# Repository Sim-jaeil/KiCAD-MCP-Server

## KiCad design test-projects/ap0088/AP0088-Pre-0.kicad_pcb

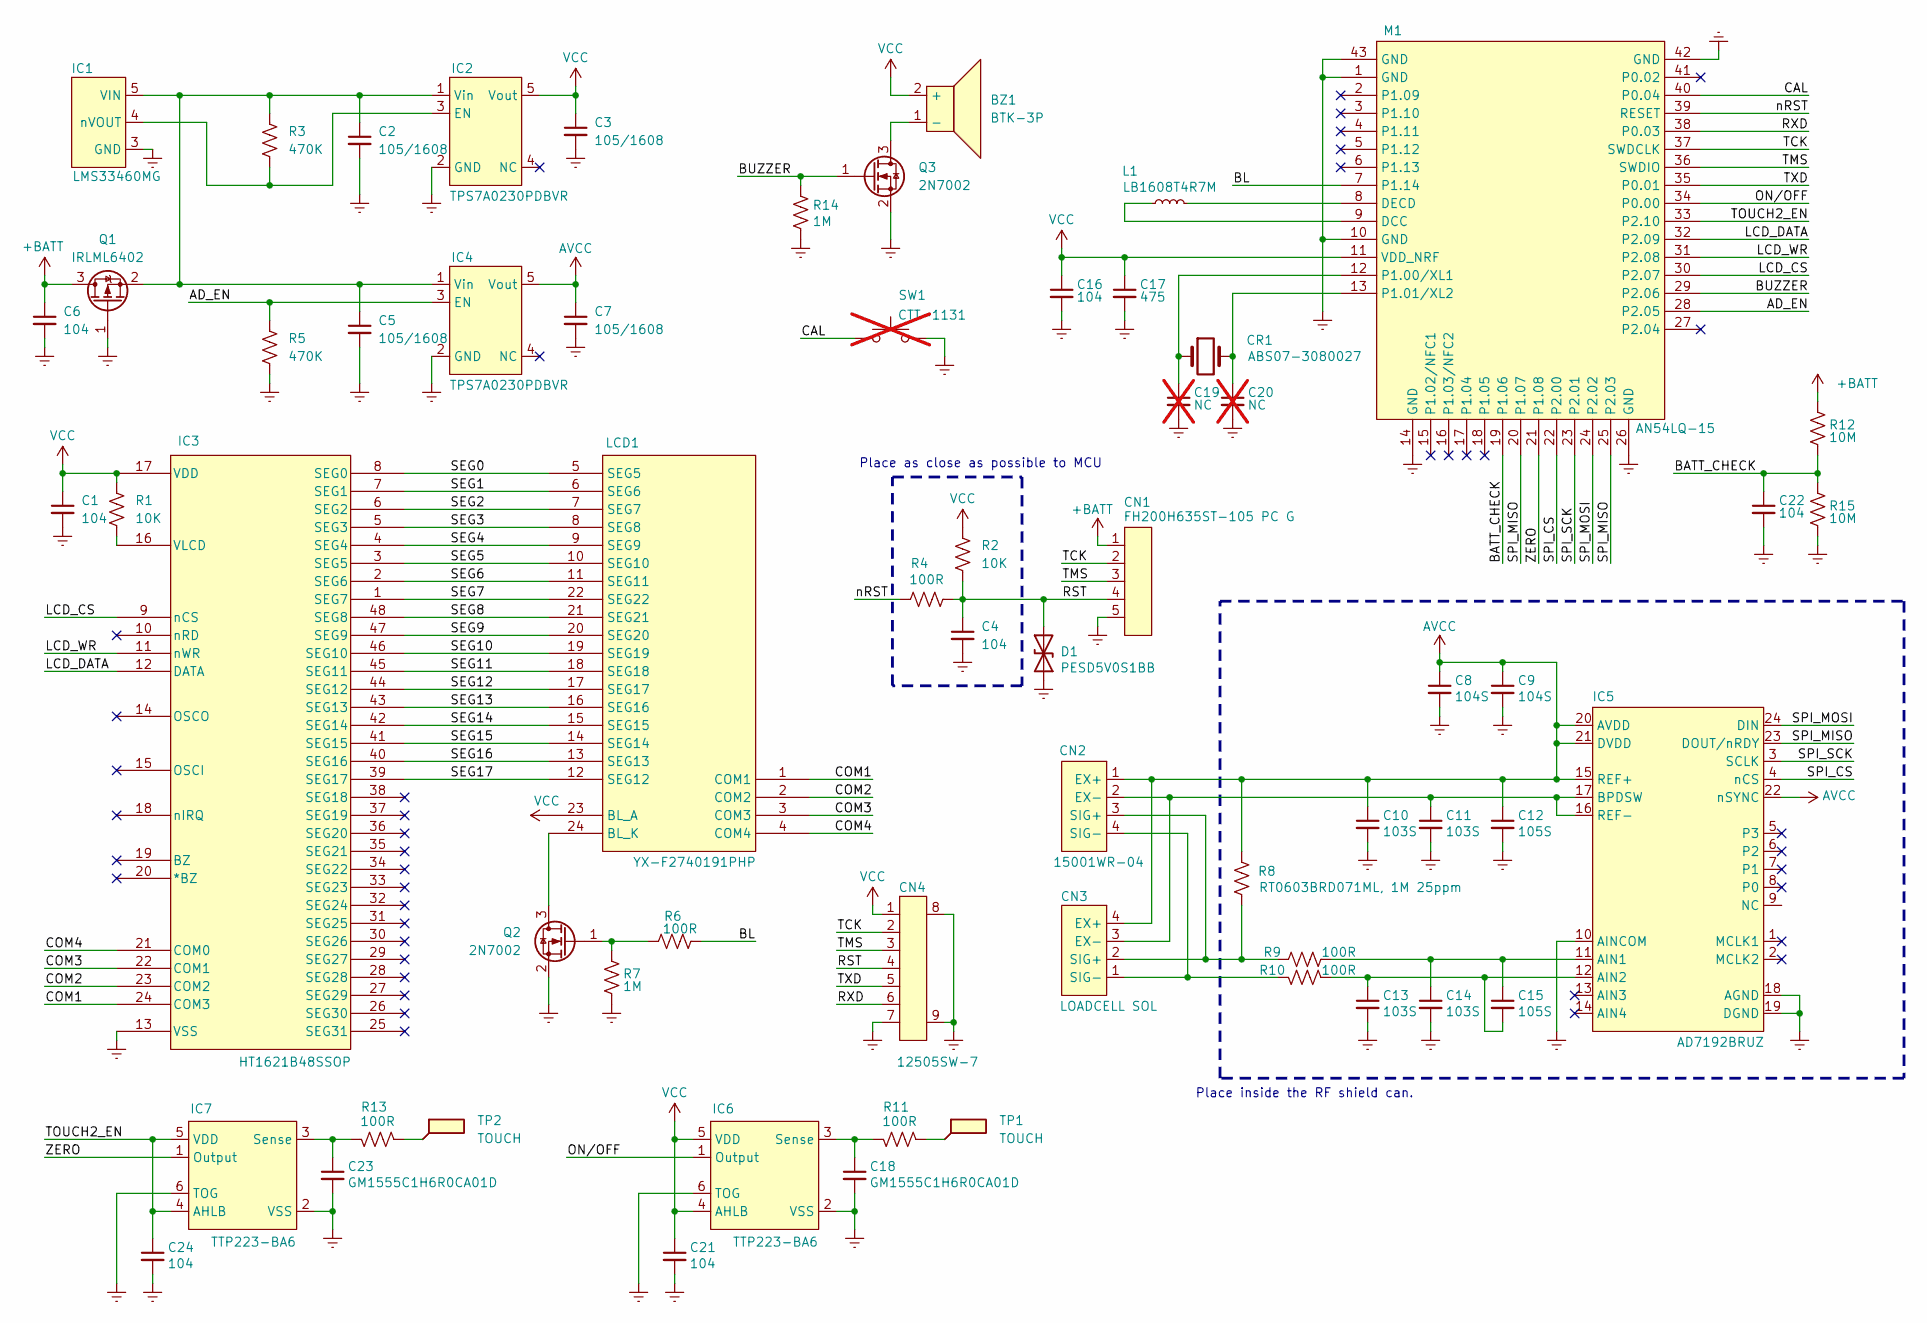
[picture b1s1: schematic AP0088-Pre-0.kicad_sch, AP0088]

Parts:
BZ1: BTK-3P
C1, C4, C6, C16, C21, C22, C24: 104; 1005C
C2, C3, C5, C7: 105/1608; 1608C
C8, C9: 104S; 1005C
C10, C11, C13, C14: 103S; 1005C
C12, C15: 105S; 1005C
C17: 475; 1608C
C18, C23: GM1555C1H6R0CA01D; 1005C
C19, C20: NC; 1005C; not fitted
CN1: FH200H635ST-105 PC G
CN2: 15001WR-04
CN3: LOADCELL SOL
CN4: 12505SW-7
CR1: ABS07-3080027; Crystal_SMD_3215-2Pin_3.2x1.5mm
D1: PESD5V0S1BB; D_SOD-523
IC1: LMS33460MG; SOT-353_SC-70-5
IC2, IC4: TPS7A0230PDBVR; SOT-23-5
IC3: HT1621B48SSOP; HT1621B
IC5: AD7192BRUZ; TSSOP-24_4.4x7.8mm_P0.65mm
IC6, IC7: TTP223-BA6
L1: LB1608T4R7M; L_0603_1608Metric
LCD1: YX-F2740191PHP; AXR-LCD
M1: AN54LQ-15
Q1: IRLML6402; SOT-23
Q2, Q3: 2N7002; SOT-23
R1, R2: 10K; 1005R
R3, R5: 470K; 1005R
R4, R6, R9, R10, R11, R13: 100R; 1005R
R7, R14: 1M; 1005R
R8: RT0603BRD071ML, 1M 25ppm; 1608R
R12, R15: 10M; 1005R
SW1: CTT-1131; not fitted
TP1, TP2: TOUCH; TOUCH_SPRING

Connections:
+BATT: C6.1, CN1.1, Q1.3 (D), R12.1
/AD_EN: IC4.3 (EN), M1.28 (P2.05), R5.2
/BATT_CHECK: C22.1, M1.19 (P1.06), R12.2, R15.1
/BL: M1.7 (P1.14), R6.2
/BUZZER: M1.29 (P2.06), Q3.1 (G), R14.1
/CAL: M1.40 (P0.04), SW1.1
/COM1: IC3.24 (COM3), LCD1.1 (COM1)
/COM2: IC3.23 (COM2), LCD1.2 (COM2)
/COM3: IC3.22 (COM1), LCD1.3 (COM3)
/COM4: IC3.21 (COM0), LCD1.4 (COM4)
/LCD_CS: IC3.9 (nCS), M1.30 (P2.07)
/LCD_DATA: IC3.12 (DATA), M1.32 (P2.09)
/LCD_WR: IC3.11 (nWR), M1.31 (P2.08)
/ON/OFF: IC6.1 (Output), M1.34 (P0.00)
/RST: C4.1, CN1.4, CN4.4, D1.2 (A2), R2.1, R4.2
/RXD: CN4.6, M1.38 (P0.03)
/SEG0: IC3.8 (SEG0), LCD1.5 (SEG5)
/SEG1: IC3.7 (SEG1), LCD1.6 (SEG6)
/SEG2: IC3.6 (SEG2), LCD1.7 (SEG7)
/SEG3: IC3.5 (SEG3), LCD1.8 (SEG8)
/SEG4: IC3.4 (SEG4), LCD1.9 (SEG9)
/SEG5: IC3.3 (SEG5), LCD1.10 (SEG10)
/SEG6: IC3.2 (SEG6), LCD1.11 (SEG11)
/SEG7: IC3.1 (SEG7), LCD1.22 (SEG22)
/SEG8: IC3.48 (SEG8), LCD1.21 (SEG21)
/SEG9: IC3.47 (SEG9), LCD1.20 (SEG20)
/SEG10: IC3.46 (SEG10), LCD1.19 (SEG19)
/SEG11: IC3.45 (SEG11), LCD1.18 (SEG18)
/SEG12: IC3.44 (SEG12), LCD1.17 (SEG17)
/SEG13: IC3.43 (SEG13), LCD1.16 (SEG16)
/SEG14: IC3.42 (SEG14), LCD1.15 (SEG15)
/SEG15: IC3.41 (SEG15), LCD1.14 (SEG14)
/SEG16: IC3.40 (SEG16), LCD1.13 (SEG13)
/SEG17: IC3.39 (SEG17), LCD1.12 (SEG12)
/SPI_CS: IC5.4 (nCS), M1.22 (P2.00)
/SPI_MISO: IC5.23 (DOUT/nRDY), M1.20 (P1.07), M1.25 (P2.03)
/SPI_MOSI: IC5.24 (DIN), M1.24 (P2.02)
/SPI_SCK: IC5.3 (SCLK), M1.23 (P2.01)
/TCK: CN1.2, CN4.2, M1.37 (SWDCLK)
/TMS: CN1.3, CN4.3, M1.36 (SWDIO)
/TOUCH2_EN: C24.1, IC7.4 (AHLB), IC7.5 (VDD), M1.33 (P2.10)
/TXD: CN4.5, M1.35 (P0.01)
/ZERO: IC7.1 (Output), M1.21 (P1.08)
/nRST: M1.39 (RESET), R4.1
AVCC: C7.1, C8.1, C9.1, C10.1, C12.1, CN2.1 (EX+), CN3.4 (EX+), IC4.5 (Vout), IC5.15 (REF+), IC5.20 (AVDD), IC5.21 (DVDD), IC5.22 (nSYNC), R8.2
Earth: C1.2, C2.2, C3.2, C4.2, C5.2, C6.2, C7.2, C8.2, C9.2, C10.2, C11.2, C12.2, C13.2, C14.2, C16.2, C17.2, C18.2, C19.2, C20.2, C21.2, C22.2, C23.2, C24.2, CN1.5, CN4.7, CN4.8, CN4.9, D1.1 (A1), IC1.3 (GND), IC2.2 (GND), IC3.13 (VSS), IC4.2 (GND), IC5.10 (AINCOM), IC5.18 (AGND), IC5.19 (DGND), IC6.2 (VSS), IC6.6 (TOG), IC7.2 (VSS), IC7.6 (TOG), M1.1 (GND), M1.10 (GND), M1.14 (GND), M1.26 (GND), M1.42 (GND), M1.43 (GND), Q1.1 (G), Q2.2 (S), Q3.2 (S), R5.1, R7.2, R14.2, R15.2, SW1.2
unnamed: BZ1.1 (-), Q3.3 (D)
unnamed: C11.1, CN2.2 (EX-), CN3.3 (EX-), IC5.16 (REF-), IC5.17 (BPDSW)
unnamed: CN2.3 (SIG+), CN3.2 (SIG+), R8.1, R9.2
unnamed: CN2.4 (SIG-), CN3.1 (SIG-), R10.2
unnamed: C2.1, C5.1, IC1.5 (VIN), IC2.1 (Vin), IC4.1 (Vin), Q1.2 (S), R3.2
unnamed: IC1.4 (nVOUT), IC2.3 (EN), R3.1
unnamed: IC3.16 (VLCD), R1.1
unnamed: C14.1, C15.1, IC5.11 (AIN1), R9.1
unnamed: C13.1, C15.2, IC5.12 (AIN2), R10.1
unnamed: C18.1, IC6.3 (Sense), R11.2
unnamed: C23.1, IC7.3 (Sense), R13.2
unnamed: LCD1.24 (BL_K), Q2.3 (D)
unnamed: L1.1, M1.9 (DCC)
unnamed: L1.2, M1.8 (DECD)
unnamed: C19.1, CR1.1, M1.12 (P1.00/XL1)
unnamed: C20.1, CR1.2, M1.13 (P1.01/XL2)
unnamed: Q2.1 (G), R6.1, R7.1
unnamed: R11.1, TP1.1 (1_1)
unnamed: R13.1, TP2.1 (1_1)
VCC: BZ1.2 (+), C1.1, C3.1, C16.1, C17.1, C21.1, CN4.1, IC2.5 (Vout), IC3.17 (VDD), IC6.4 (AHLB), IC6.5 (VDD), LCD1.23 (BL_A), M1.11 (VDD_NRF), R1.2, R2.2

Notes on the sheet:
Place as close as possible to MCU
Place inside the RF shield can.

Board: 2 copper layers, 61 parts (57 on the bottom side), 66 nets, no tracks yet.

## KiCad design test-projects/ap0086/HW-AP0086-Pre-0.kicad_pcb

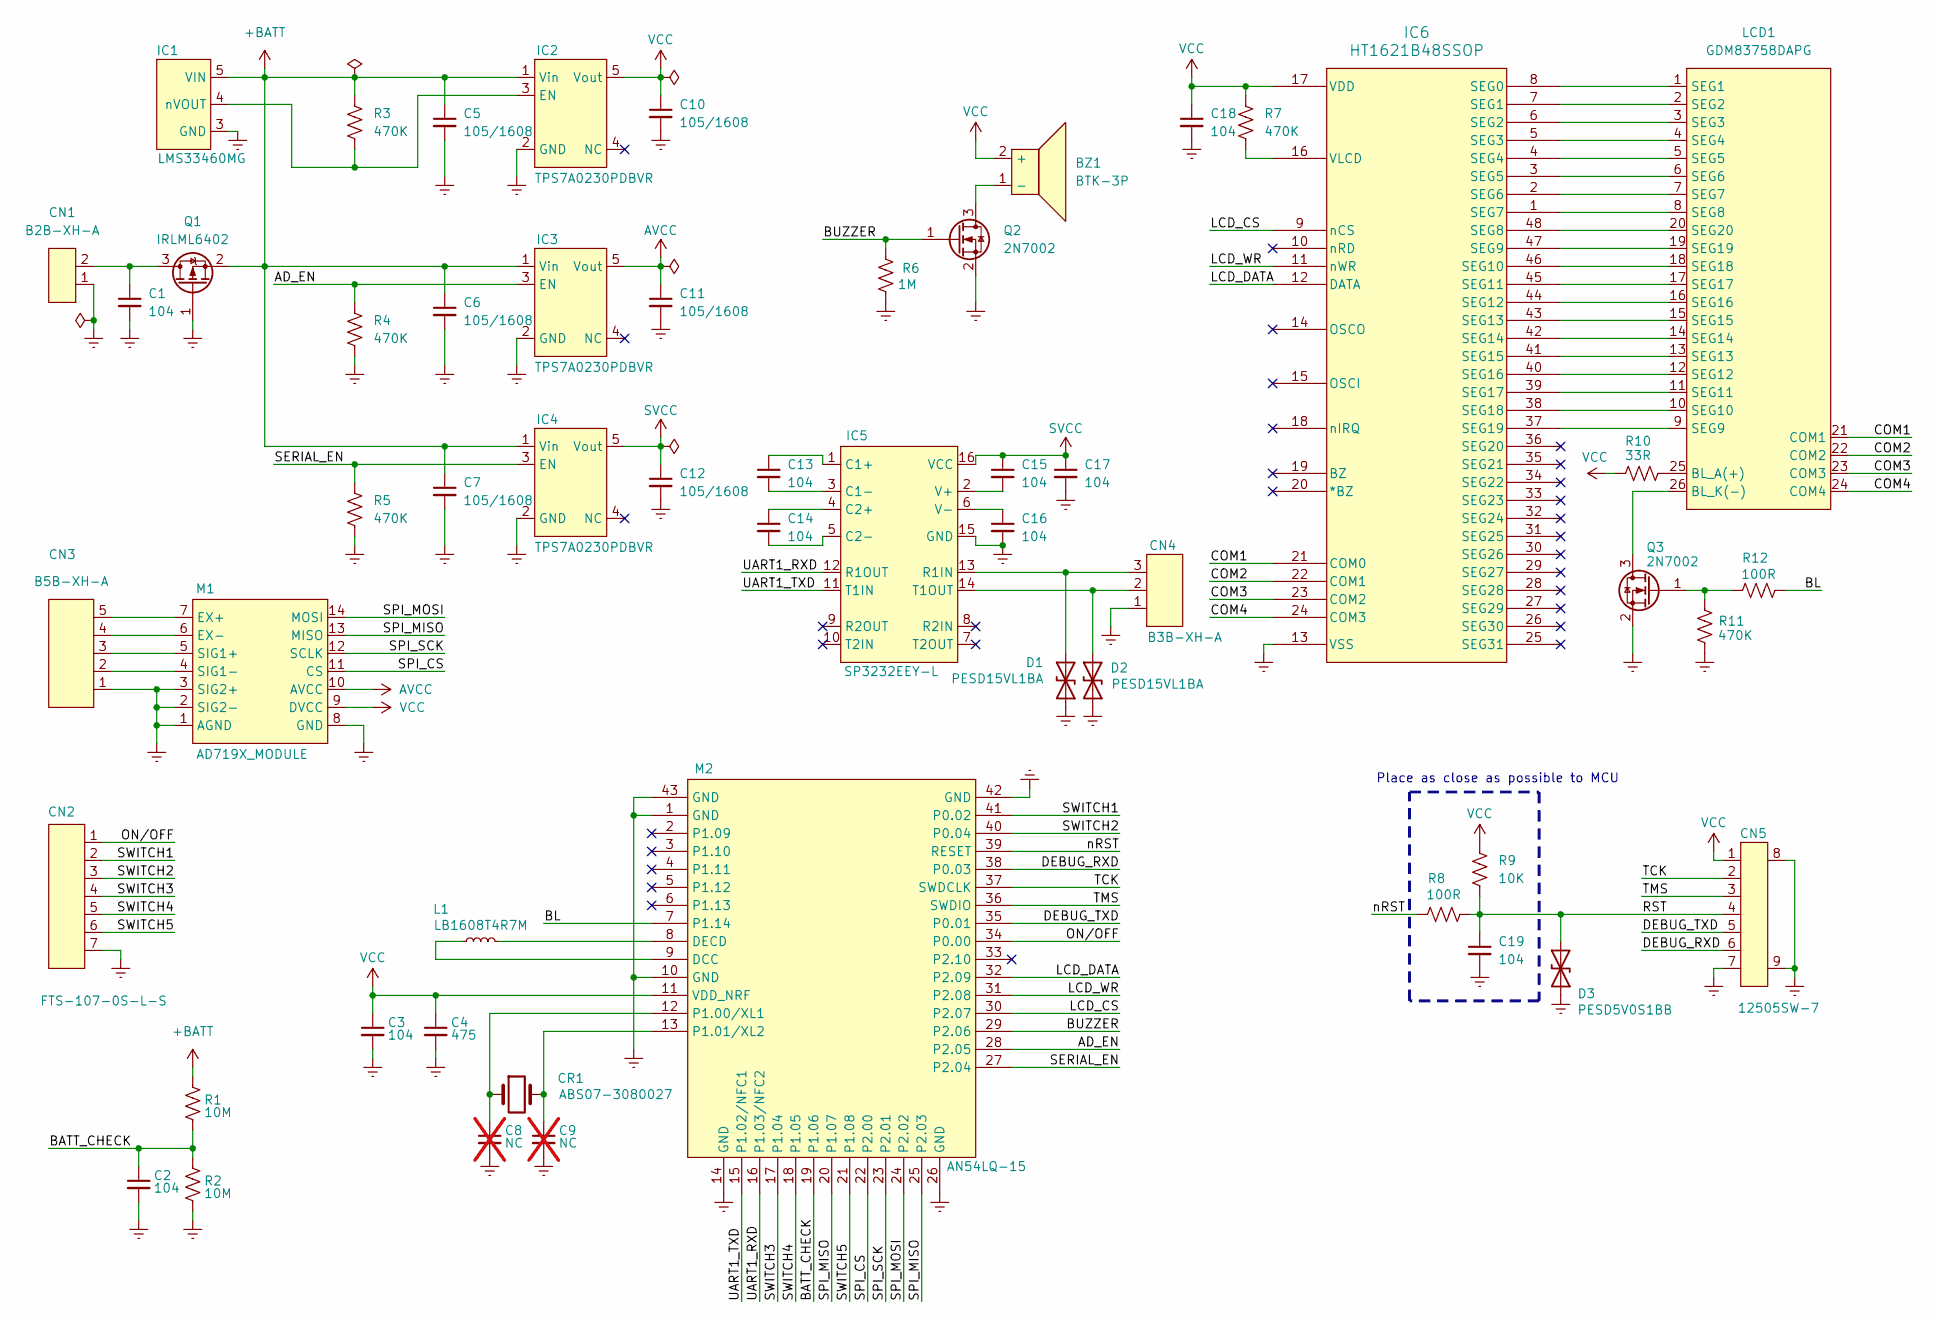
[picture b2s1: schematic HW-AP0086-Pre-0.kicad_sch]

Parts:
BZ1: BTK-3P
C1, C2, C3, C13, C14, C15, C16, C17, C18, C19: 104; 1005C
C4: 475; 1005C
C5, C6, C7, C10, C11, C12: 105/1608; 1608C
C8, C9: NC; 1005C; not fitted
CN1: B2B-XH-A; JST_XH_B2B-XH-A_1x02_P2.50mm_Vertical
CN2: FTS-107-0S-L-S
CN3: B5B-XH-A; JST_XH_B5B-XH-A_1x05_P2.50mm_Vertical
CN4: B3B-XH-A
CN5: 12505SW-7
CR1: ABS07-3080027; Crystal_SMD_3215-2Pin_3.2x1.5mm
D1, D2: PESD15VL1BA; D_SOD-523
D3: PESD5V0S1BB; D_SOD-523
IC1: LMS33460MG; SOT-353_SC-70-5
IC2, IC3, IC4: TPS7A0230PDBVR; SOT-23-5
IC5: SP3232EEY-L; SP3232EEY-L_TSSOP16
IC6: HT1621B48SSOP; HT1621B
L1: LB1608T4R7M; L_0603_1608Metric
LCD1: GDM83758DAPG; ANYLOAD-LCD
M1: AD719X_MODULE; AD719X-Module
M2: AN54LQ-15
Q1: IRLML6402; SOT-23
Q2, Q3: 2N7002; SOT-23
R1, R2: 10M; R_0402_1005Metric
R3, R4, R5, R7, R11: 470K; 1005R
R6: 1M; R_0402_1005Metric
R8, R12: 100R; 1005R
R9: 10K; 1005R
R10: 33R; 1005R

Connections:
+BATT: C5.1, C6.1, C7.1, IC1.5 (VIN), IC2.1 (Vin), IC3.1 (Vin), IC4.1 (Vin), Q1.2 (S), R1.1, R3.2
/AD_EN: IC3.3 (EN), M2.28 (P2.05), R4.2
/BATT_CHECK: C2.1, M2.19 (P1.06), R1.2, R2.1
/BL: M2.7 (P1.14), R12.1
/BUZZER: M2.29 (P2.06), Q2.1 (G), R6.1
/COM1: IC6.21 (COM0), LCD1.21 (COM1)
/COM2: IC6.22 (COM1), LCD1.22 (COM2)
/COM3: IC6.23 (COM2), LCD1.23 (COM3)
/COM4: IC6.24 (COM3), LCD1.24 (COM4)
/DEBUG_RXD: CN5.6, M2.38 (P0.03)
/DEBUG_TXD: CN5.5, M2.35 (P0.01)
/LCD_CS: IC6.9 (nCS), M2.30 (P2.07)
/LCD_DATA: IC6.12 (DATA), M2.32 (P2.09)
/LCD_WR: IC6.11 (nWR), M2.31 (P2.08)
/ON/OFF: CN2.1, M2.34 (P0.00)
/RST: C19.1, CN5.4, D3.2 (A2), R8.2, R9.1
/SERIAL_EN: IC4.3 (EN), M2.27 (P2.04), R5.2
/SPI_CS: M1.11 (CS), M2.22 (P2.00)
/SPI_MISO: M1.13 (MISO), M2.20 (P1.07), M2.25 (P2.03)
/SPI_MOSI: M1.14 (MOSI), M2.24 (P2.02)
/SPI_SCK: M1.12 (SCLK), M2.23 (P2.01)
/SWITCH1: CN2.2, M2.41 (P0.02)
/SWITCH2: CN2.3, M2.40 (P0.04)
/SWITCH3: CN2.4, M2.17 (P1.04)
/SWITCH4: CN2.5, M2.18 (P1.05)
/SWITCH5: CN2.6, M2.21 (P1.08)
/TCK: CN5.2, M2.37 (SWDCLK)
/TMS: CN5.3, M2.36 (SWDIO)
/UART1_RXD: IC5.12 (R1OUT), M2.16 (P1.03/NFC2)
/UART1_TXD: IC5.11 (T1IN), M2.15 (P1.02/NFC1)
/nRST: M2.39 (RESET), R8.1
AVCC: C11.1, IC3.5 (Vout), M1.10 (AVCC)
Earth: C1.2, C2.2, C3.2, C4.2, C5.2, C6.2, C7.2, C8.2, C9.2, C10.2, C11.2, C12.2, C16.2, C17.2, C18.2, C19.2, CN1.1, CN2.7, CN3.1, CN4.1, CN5.7, CN5.8, CN5.9, D1.1 (A1), D2.1 (A1), D3.1 (A1), IC1.3 (GND), IC2.2 (GND), IC3.2 (GND), IC4.2 (GND), IC5.15 (GND), IC6.13 (VSS), M1.1 (AGND), M1.2 (SIG2-), M1.3 (SIG2+), M1.8 (GND), M2.1 (GND), M2.10 (GND), M2.14 (GND), M2.26 (GND), M2.42 (GND), M2.43 (GND), Q1.1 (G), Q2.2 (S), Q3.2 (S), R2.2, R4.1, R5.1, R6.2, R11.2
unnamed: BZ1.1 (-), Q2.3 (D)
unnamed: CN4.3, D1.2 (A2), IC5.13 (R1IN)
unnamed: CN4.2, D2.2 (A2), IC5.14 (T1OUT)
unnamed: IC1.4 (nVOUT), IC2.3 (EN), R3.1
unnamed: C13.1, IC5.1 (C1+)
unnamed: C13.2, IC5.3 (C1-)
unnamed: C14.1, IC5.4 (C2+)
unnamed: C14.2, IC5.5 (C2-)
unnamed: C15.2, IC5.2 (V+)
unnamed: C16.1, IC5.6 (V-)
unnamed: IC6.8 (SEG0), LCD1.1 (SEG1)
unnamed: IC6.7 (SEG1), LCD1.2 (SEG2)
unnamed: IC6.6 (SEG2), LCD1.3 (SEG3)
unnamed: IC6.5 (SEG3), LCD1.4 (SEG4)
unnamed: IC6.4 (SEG4), LCD1.5 (SEG5)
unnamed: IC6.3 (SEG5), LCD1.6 (SEG6)
unnamed: IC6.2 (SEG6), LCD1.7 (SEG7)
unnamed: IC6.1 (SEG7), LCD1.8 (SEG8)
unnamed: IC6.48 (SEG8), LCD1.20 (SEG20)
unnamed: IC6.47 (SEG9), LCD1.19 (SEG19)
unnamed: IC6.46 (SEG10), LCD1.18 (SEG18)
unnamed: IC6.45 (SEG11), LCD1.17 (SEG17)
unnamed: IC6.44 (SEG12), LCD1.16 (SEG16)
unnamed: IC6.43 (SEG13), LCD1.15 (SEG15)
unnamed: IC6.42 (SEG14), LCD1.14 (SEG14)
unnamed: IC6.41 (SEG15), LCD1.13 (SEG13)
unnamed: IC6.40 (SEG16), LCD1.12 (SEG12)
unnamed: IC6.39 (SEG17), LCD1.11 (SEG11)
unnamed: IC6.38 (SEG18), LCD1.10 (SEG10)
unnamed: IC6.37 (SEG19), LCD1.9 (SEG9)
unnamed: IC6.16 (VLCD), R7.1
unnamed: LCD1.25 (BL_A(+)), R10.1
unnamed: LCD1.26 (BL_K(-)), Q3.3 (D)
unnamed: CN3.5, M1.7 (EX+)
unnamed: CN3.4, M1.6 (EX-)
unnamed: CN3.3, M1.5 (SIG1+)
unnamed: CN3.2, M1.4 (SIG1-)
unnamed: L1.1, M2.9 (DCC)
unnamed: L1.2, M2.8 (DECD)
unnamed: C8.1, CR1.1, M2.12 (P1.00/XL1)
unnamed: C9.1, CR1.2, M2.13 (P1.01/XL2)
unnamed: C1.1, CN1.2, Q1.3 (D)
unnamed: Q3.1 (G), R11.1, R12.2
SVCC: C12.1, C15.1, C17.1, IC4.5 (Vout), IC5.16 (VCC)
VCC: BZ1.2 (+), C3.1, C4.1, C10.1, C18.1, CN5.1, IC2.5 (Vout), IC6.17 (VDD), M1.9 (DVCC), M2.11 (VDD_NRF), R7.2, R9.2, R10.2

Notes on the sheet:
Place as close as possible to MCU

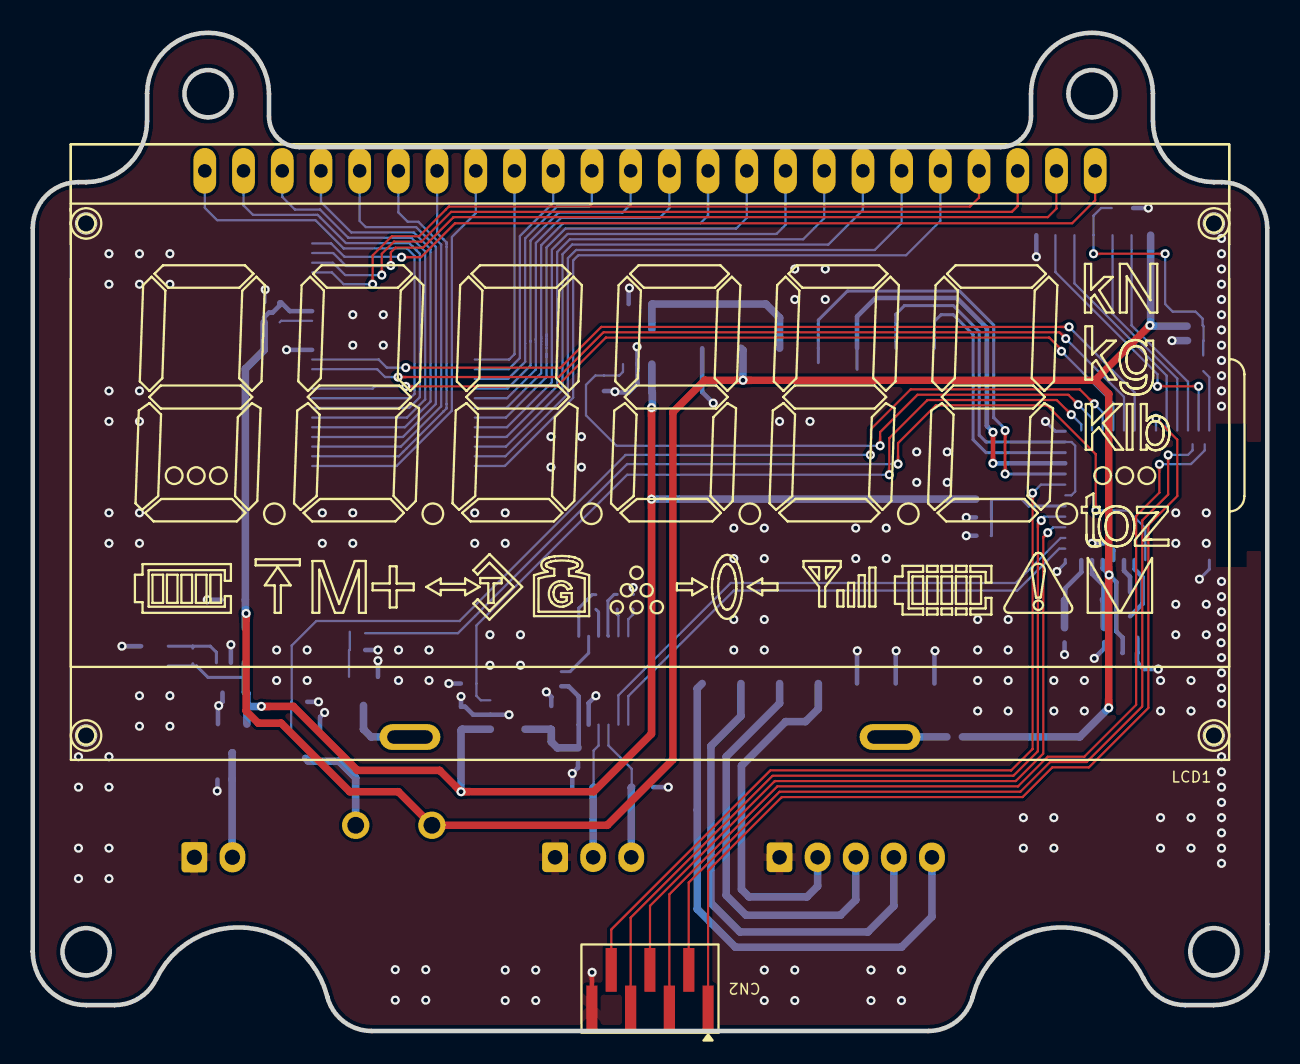
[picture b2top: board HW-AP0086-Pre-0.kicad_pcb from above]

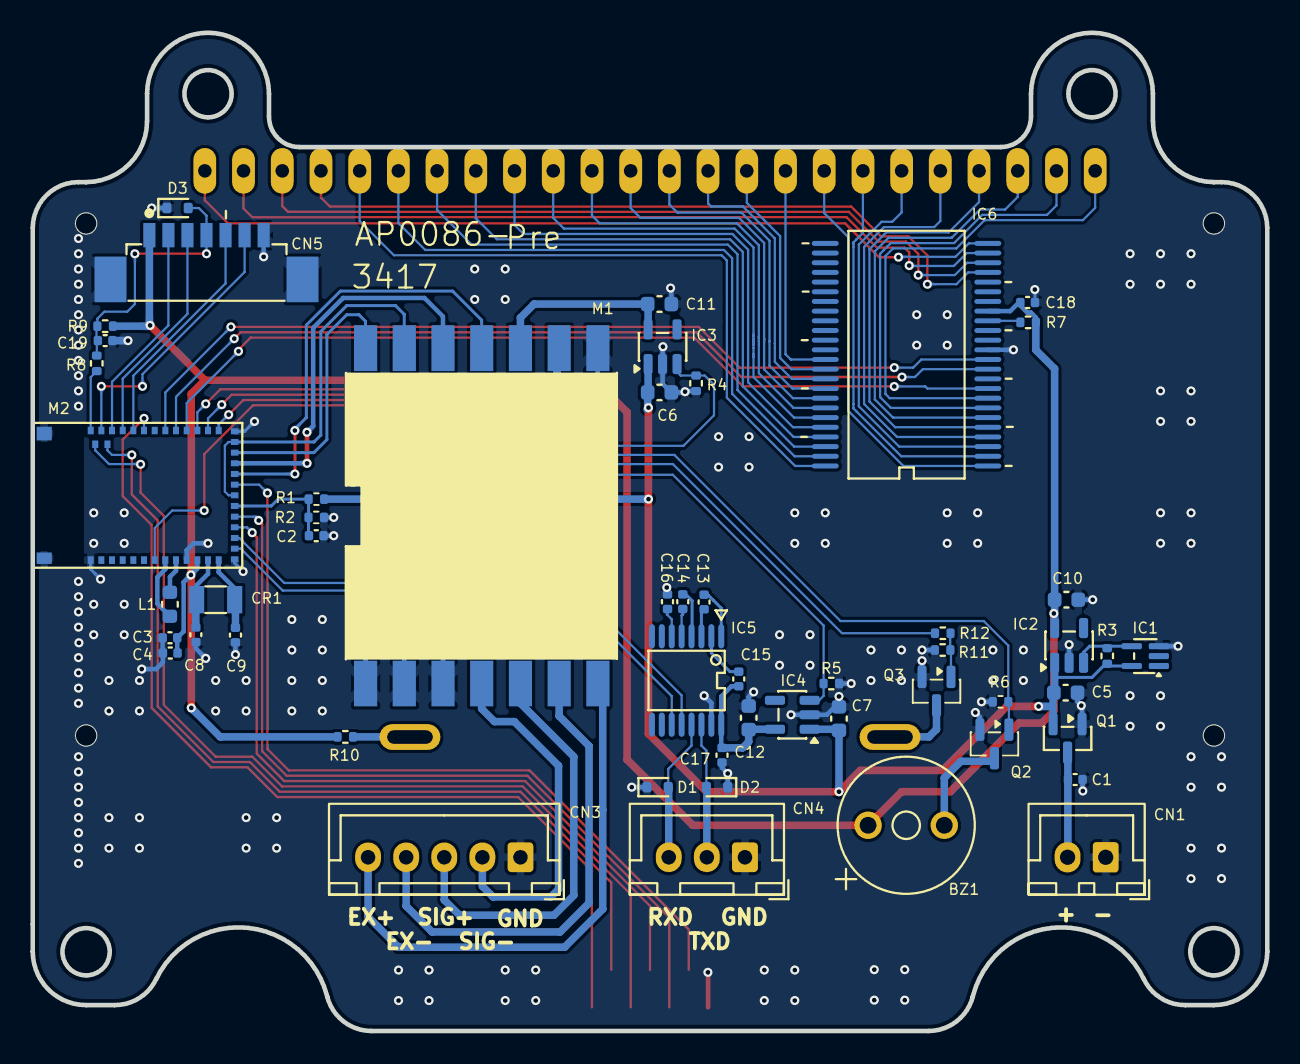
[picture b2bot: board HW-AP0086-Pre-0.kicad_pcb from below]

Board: 2 copper layers, 81.0 x 65.5 mm, 54 parts (52 on the bottom side), 78 nets.

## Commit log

2026-03-10 chore: fork KiCAD-MCP-Server and setup macOS dev environment
2026-03-10 test: add test projects for circuit review validation
2026-03-10 docs: add architecture analysis of forked KiCAD-MCP-Server
